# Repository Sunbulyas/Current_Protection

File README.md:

# Current_Protection
The project is about current projection for a system that does not known. 

Firstly, I desccripted the problem on the system. Then, I searched and found this solving. 
The problem is that the system shuts down before a problem occurs due to high current in the system.
Secondly, I have identified the appropriate components. The main components are current transformer and OpAMP.

In the solution of this problem, we first provide isolation from our circuit with the voltage follower with the signal coming from the current transformer. 
Then, with the ongoing signal, we ensure that the system works with a comparator opamp with the appropriate output according to the voltage level we want.

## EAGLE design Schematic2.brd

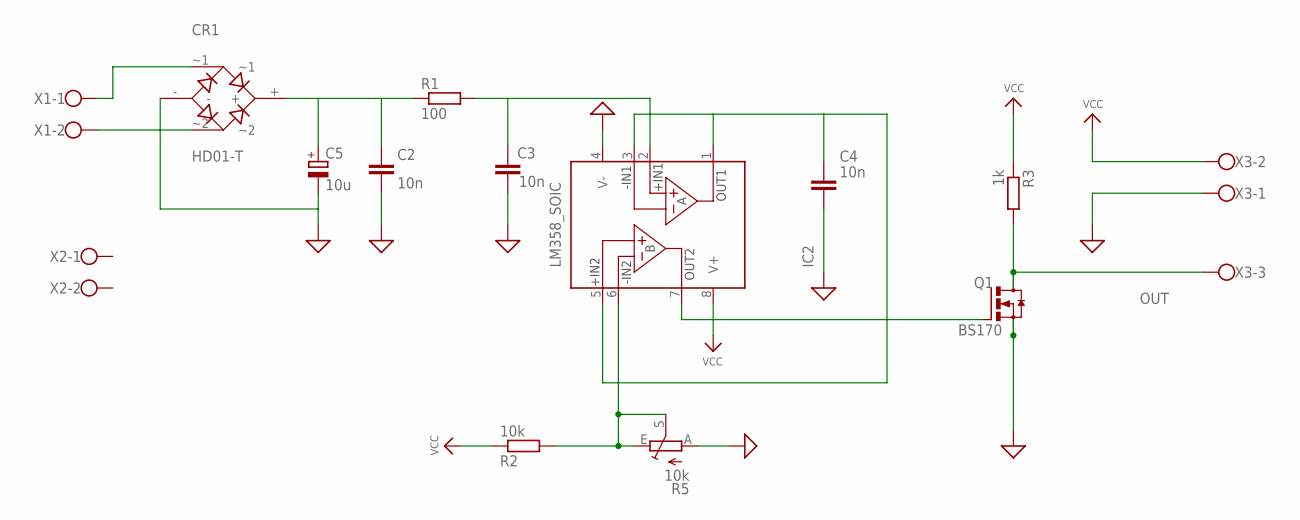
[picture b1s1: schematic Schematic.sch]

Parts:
C2, C3, C4: 10n; CAPC1608X85
C5: 10u; 140CLH-1010
CR1: HD01-T
IC2: LM358_SOIC; SOIC127P600X175-8N
Q1: BS170; TO92-3
R1: 100; R0603
R2: 10k; R0603
R3: 1k; R0603
R5: 10k; SP19L
X1, X2: W237-102
X3: W237-103

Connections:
GND: C2.2, C3.2, C4.2, C5.-, CR1.-, IC2.4 (V-), Q1.3 (S), R5.A, X3.1
unnamed: C2.1, C5.+, CR1.+, R1.1
unnamed: C3.1, IC2.2 (-IN1), R1.2
unnamed: IC2.6 (-IN2), R2.2, R5.E, R5.S
unnamed: C4.1, IC2.1 (OUT1), IC2.3 (+IN1), IC2.5 (+IN2)
unnamed: CR1.~1, X1.1
unnamed: IC2.7 (OUT2), Q1.2 (G)
unnamed: CR1.~2, X1.2
OUT: Q1.1 (D), R3.2, X3.3
VCC: IC2.8 (V+), R2.1, R3.1, X3.2

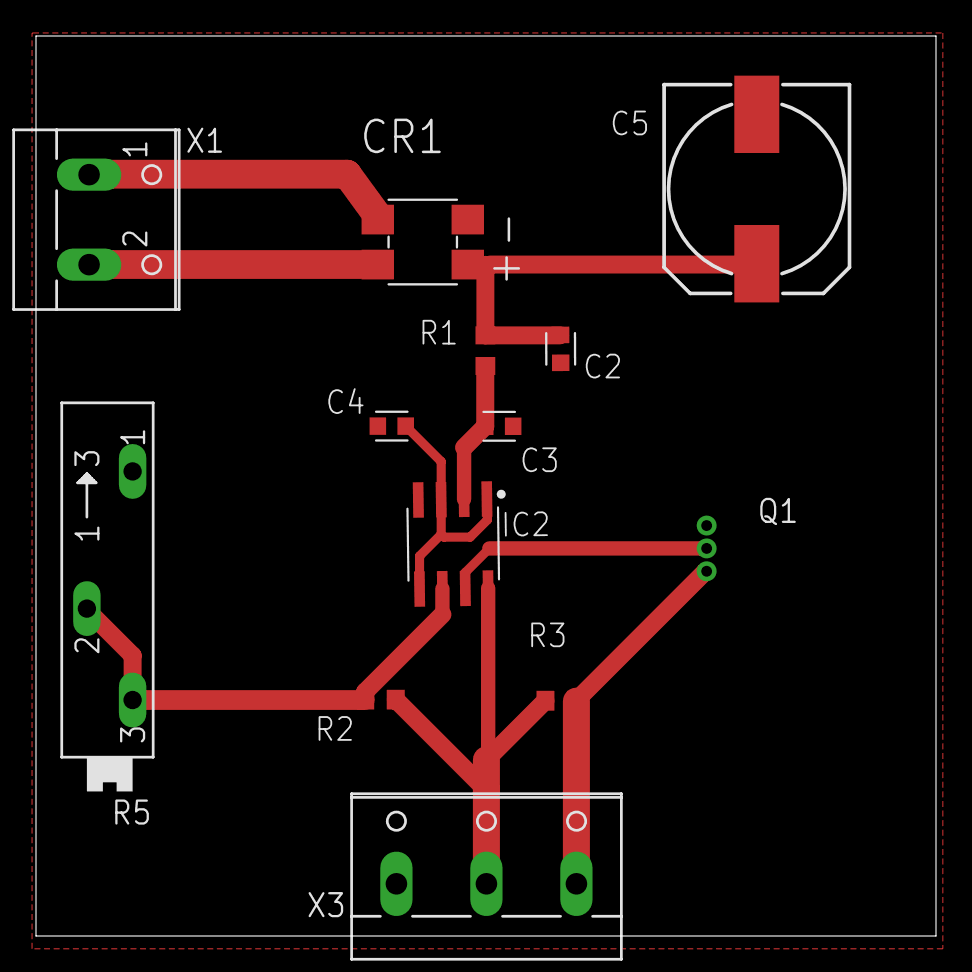
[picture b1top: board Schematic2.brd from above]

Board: 2 copper layers, 50.0 x 50.0 mm, 13 parts (1 on the bottom side), 10 nets.
